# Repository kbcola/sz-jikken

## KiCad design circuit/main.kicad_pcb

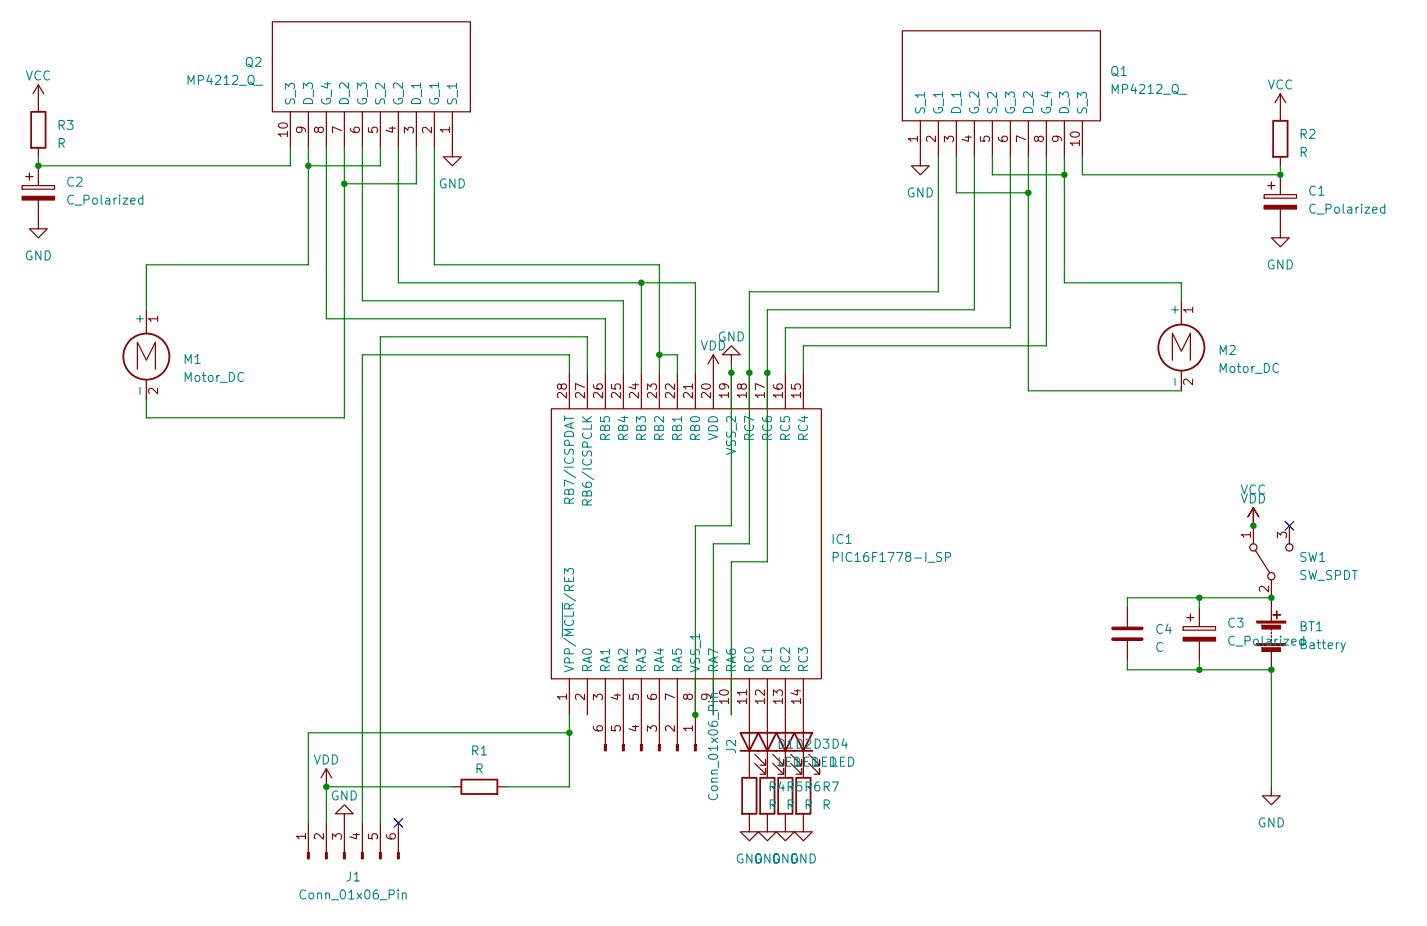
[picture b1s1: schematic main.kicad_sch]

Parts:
BT1: Battery; PinHeader_1x02_P2.54mm_Horizontal
C1, C2, C3: C_Polarized; CP_Radial_D5.0mm_P2.00mm
C4: C; C_Disc_D5.0mm_W2.5mm_P5.00mm
D1, D2, D3, D4: LED; LED_D3.0mm
IC1: PIC16F1778-I_SP; DIP-28_W7.62mm_LongPads; Manufacturer_Part_Number PIC16F1778-I/SP; Mouser Part Number 579-PIC16F1778-I/SP
J1, J2: Conn_01x06_Pin; PinHeader_1x06_P2.54mm_Vertical
M1, M2: Motor_DC; PinHeader_1x02_P2.54mm_Horizontal
Q1, Q2: MP4212_Q_; MP4212Q; Manufacturer_Part_Number MP4212(Q); Mouser Part Number N/A
R1, R4, R5, R6, R7: R; R_Axial_DIN0207_L6.3mm_D2.5mm_P7.62mm_Horizontal
R2, R3: R; R_Axial_DIN0309_L9.0mm_D3.2mm_P12.70mm_Horizontal
SW1: SW_SPDT; ToggleSW_3pin

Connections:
GND: BT1.2 (-), C1.2, C2.2, C3.2, C4.2, IC1.8 (VSS_1), IC1.19 (VSS_2), J1.3, J2.1, Q1.1 (S_1), Q2.1 (S_1), R4.2, R5.2, R6.2, R7.2
unnamed: BT1.1 (+), C3.1, C4.1, SW1.2 (B)
unnamed: D1.2 (A), IC1.11 (RC0)
unnamed: D1.1 (K), R4.1
unnamed: D2.2 (A), IC1.12 (RC1)
unnamed: D2.1 (K), R5.1
unnamed: D3.2 (A), IC1.13 (RC2)
unnamed: D3.1 (K), R6.1
unnamed: D4.2 (A), IC1.14 (RC3)
unnamed: D4.1 (K), R7.1
unnamed: IC1.3 (RA1), J2.6
unnamed: IC1.4 (RA2), J2.5
unnamed: IC1.5 (RA3), J2.4
unnamed: IC1.6 (RA4), J2.3
unnamed: IC1.7 (RA5), J2.2
unnamed: IC1.10 (RA6), IC1.17 (RC6), Q1.4 (G_2)
unnamed: IC1.9 (RA7), IC1.18 (RC7), Q1.2 (G_1)
unnamed: IC1.21 (RB0), IC1.24 (RB3), Q2.4 (G_2)
unnamed: IC1.22 (RB1), IC1.23 (RB2), Q2.2 (G_1)
unnamed: IC1.25 (RB4), Q2.6 (G_3)
unnamed: IC1.26 (RB5), Q2.8 (G_4)
unnamed: IC1.27 (RB6/ICSPCLK), J1.5
unnamed: IC1.28 (RB7/ICSPDAT), J1.4
unnamed: IC1.15 (RC4), Q1.8 (G_4)
unnamed: IC1.16 (RC5), Q1.6 (G_3)
unnamed: IC1.1 (VPP/~MCLR/RE3), J1.1, R1.2
unnamed: M1.1 (+), Q2.5 (S_2), Q2.9 (D_3)
unnamed: M1.2 (-), Q2.3 (D_1), Q2.7 (D_2)
unnamed: M2.1 (+), Q1.5 (S_2), Q1.9 (D_3)
unnamed: M2.2 (-), Q1.3 (D_1), Q1.7 (D_2)
unnamed: C1.1, Q1.10 (S_3), R2.2
unnamed: C2.1, Q2.10 (S_3), R3.2
VCC: IC1.20 (VDD), J1.2, R1.1, R2.1, R3.1, SW1.1 (A)

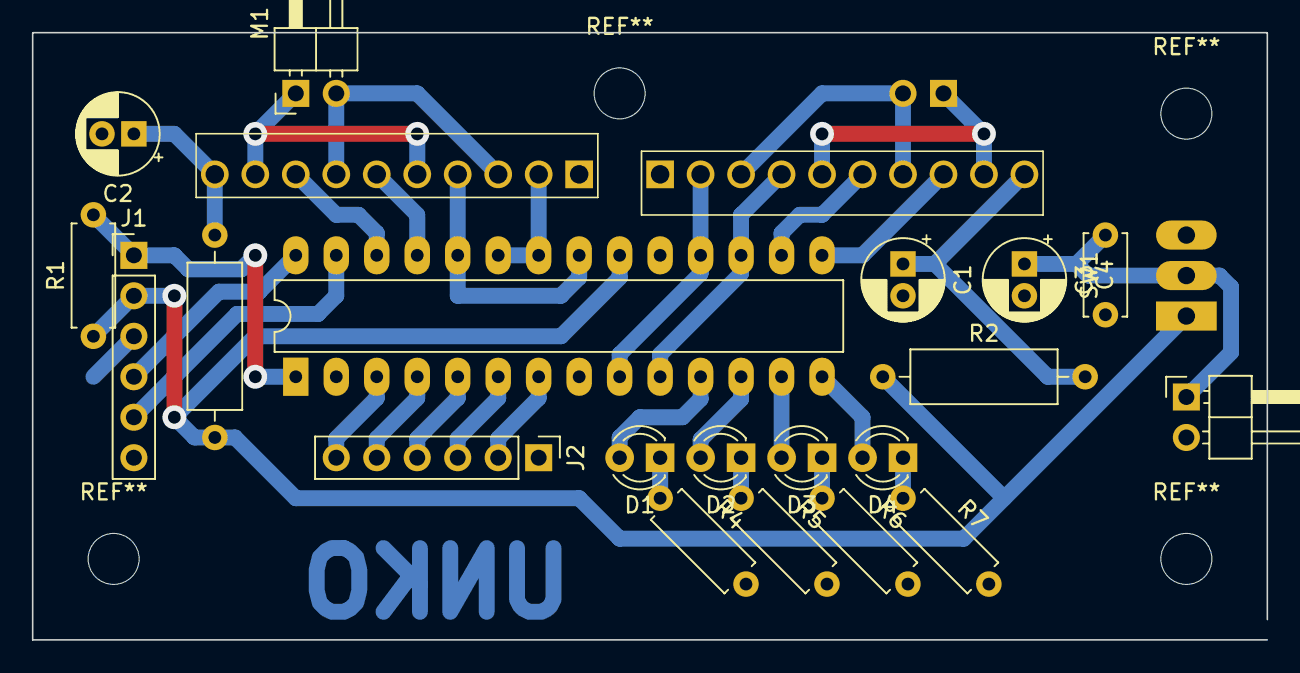
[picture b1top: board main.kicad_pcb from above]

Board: 2 copper layers, 77.5 x 38.1 mm, 24 parts (1 on the bottom side), 33 nets.

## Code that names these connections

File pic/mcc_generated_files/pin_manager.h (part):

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// get/set SAENS_LD aliases
#define SAENS_LD_TRIS                 TRISAbits.TRISA1
#define SAENS_LD_LAT                  LATAbits.LATA1
#define SAENS_LD_PORT                 PORTAbits.RA1
#define SAENS_LD_WPU                  WPUAbits.WPUA1
#define SAENS_LD_OD                   ODCONAbits.ODA1
#define SAENS_LD_ANS                  ANSELAbits.ANSA1
#define SAENS_LD_SetHigh()            do { LATAbits.LATA1 = 1; } while(0)
#define SAENS_LD_SetLow()             do { LATAbits.LATA1 = 0; } while(0)
#define SAENS_LD_Toggle()             do { LATAbits.LATA1 = ~LATAbits.LATA1; } while(0)
#define SAENS_LD_GetValue()           PORTAbits.RA1
#define SAENS_LD_SetDigitalInput()    do { TRISAbits.TRISA1 = 1; } while(0)
#define SAENS_LD_SetDigitalOutput()   do { TRISAbits.TRISA1 = 0; } while(0)
#define SAENS_LD_SetPullup()          do { WPUAbits.WPUA1 = 1; } while(0)
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// get/set SAENS_LA aliases
#define SAENS_LA_TRIS                 TRISAbits.TRISA2
#define SAENS_LA_LAT                  LATAbits.LATA2
#define SAENS_LA_PORT                 PORTAbits.RA2
#define SAENS_LA_WPU                  WPUAbits.WPUA2
#define SAENS_LA_OD                   ODCONAbits.ODA2
#define SAENS_LA_ANS                  ANSELAbits.ANSA2
#define SAENS_LA_SetHigh()            do { LATAbits.LATA2 = 1; } while(0)
#define SAENS_LA_SetLow()             do { LATAbits.LATA2 = 0; } while(0)
#define SAENS_LA_Toggle()             do { LATAbits.LATA2 = ~LATAbits.LATA2; } while(0)
#define SAENS_LA_GetValue()           PORTAbits.RA2
#define SAENS_LA_SetDigitalInput()    do { TRISAbits.TRISA2 = 1; } while(0)
#define SAENS_LA_SetDigitalOutput()   do { TRISAbits.TRISA2 = 0; } while(0)
#define SAENS_LA_SetPullup()          do { WPUAbits.WPUA2 = 1; } while(0)
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// get/set SAENS_RA aliases
#define SAENS_RA_TRIS                 TRISAbits.TRISA3
#define SAENS_RA_LAT                  LATAbits.LATA3
#define SAENS_RA_PORT                 PORTAbits.RA3
#define SAENS_RA_WPU                  WPUAbits.WPUA3
#define SAENS_RA_OD                   ODCONAbits.ODA3
#define SAENS_RA_ANS                  ANSELAbits.ANSA3
#define SAENS_RA_SetHigh()            do { LATAbits.LATA3 = 1; } while(0)
#define SAENS_RA_SetLow()             do { LATAbits.LATA3 = 0; } while(0)
#define SAENS_RA_Toggle()             do { LATAbits.LATA3 = ~LATAbits.LATA3; } while(0)
#define SAENS_RA_GetValue()           PORTAbits.RA3
#define SAENS_RA_SetDigitalInput()    do { TRISAbits.TRISA3 = 1; } while(0)
#define SAENS_RA_SetDigitalOutput()   do { TRISAbits.TRISA3 = 0; } while(0)
#define SAENS_RA_SetPullup()          do { WPUAbits.WPUA3 = 1; } while(0)
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// get/set SAENS_RD aliases
#define SAENS_RD_TRIS                 TRISAbits.TRISA4
#define SAENS_RD_LAT                  LATAbits.LATA4
#define SAENS_RD_PORT                 PORTAbits.RA4
#define SAENS_RD_WPU                  WPUAbits.WPUA4
#define SAENS_RD_OD                   ODCONAbits.ODA4
#define SAENS_RD_ANS                  ANSELAbits.ANSA4
#define SAENS_RD_SetHigh()            do { LATAbits.LATA4 = 1; } while(0)
#define SAENS_RD_SetLow()             do { LATAbits.LATA4 = 0; } while(0)
#define SAENS_RD_Toggle()             do { LATAbits.LATA4 = ~LATAbits.LATA4; } while(0)
#define SAENS_RD_GetValue()           PORTAbits.RA4
#define SAENS_RD_SetDigitalInput()    do { TRISAbits.TRISA4 = 1; } while(0)
#define SAENS_RD_SetDigitalOutput()   do { TRISAbits.TRISA4 = 0; } while(0)
#define SAENS_RD_SetPullup()          do { WPUAbits.WPUA4 = 1; } while(0)
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// get/set R0 aliases
#define R0_TRIS                 TRISAbits.TRISA6
#define R0_LAT                  LATAbits.LATA6
#define R0_PORT                 PORTAbits.RA6
#define R0_WPU                  WPUAbits.WPUA6
#define R0_OD                   ODCONAbits.ODA6
#define R0_SetHigh()            do { LATAbits.LATA6 = 1; } while(0)
#define R0_SetLow()             do { LATAbits.LATA6 = 0; } while(0)
#define R0_Toggle()             do { LATAbits.LATA6 = ~LATAbits.LATA6; } while(0)
#define R0_GetValue()           PORTAbits.RA6
#define R0_SetDigitalInput()    do { TRISAbits.TRISA6 = 1; } while(0)
#define R0_SetDigitalOutput()   do { TRISAbits.TRISA6 = 0; } while(0)
#define R0_SetPullup()          do { WPUAbits.WPUA6 = 1; } while(0)
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// get/set R1 aliases
#define R1_TRIS                 TRISAbits.TRISA7
#define R1_LAT                  LATAbits.LATA7
#define R1_PORT                 PORTAbits.RA7
#define R1_WPU                  WPUAbits.WPUA7
#define R1_OD                   ODCONAbits.ODA7
#define R1_SetHigh()            do { LATAbits.LATA7 = 1; } while(0)
#define R1_SetLow()             do { LATAbits.LATA7 = 0; } while(0)
#define R1_Toggle()             do { LATAbits.LATA7 = ~LATAbits.LATA7; } while(0)
#define R1_GetValue()           PORTAbits.RA7
#define R1_SetDigitalInput()    do { TRISAbits.TRISA7 = 1; } while(0)
#define R1_SetDigitalOutput()   do { TRISAbits.TRISA7 = 0; } while(0)
#define R1_SetPullup()          do { WPUAbits.WPUA7 = 1; } while(0)
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// get/set L0 aliases
#define L0_TRIS                 TRISBbits.TRISB0
#define L0_LAT                  LATBbits.LATB0
#define L0_PORT                 PORTBbits.RB0
#define L0_WPU                  WPUBbits.WPUB0
#define L0_ANS                  ANSELBbits.ANSB0
#define L0_SetHigh()            do { LATBbits.LATB0 = 1; } while(0)
#define L0_SetLow()             do { LATBbits.LATB0 = 0; } while(0)
#define L0_Toggle()             do { LATBbits.LATB0 = ~LATBbits.LATB0; } while(0)
#define L0_GetValue()           PORTBbits.RB0
#define L0_SetDigitalInput()    do { TRISBbits.TRISB0 = 1; } while(0)
#define L0_SetDigitalOutput()   do { TRISBbits.TRISB0 = 0; } while(0)
#define L0_SetPullup()          do { WPUBbits.WPUB0 = 1; } while(0)
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// get/set L1 aliases
#define L1_TRIS                 TRISBbits.TRISB1
#define L1_LAT                  LATBbits.LATB1
#define L1_PORT                 PORTBbits.RB1
#define L1_WPU                  WPUBbits.WPUB1
#define L1_ANS                  ANSELBbits.ANSB1
#define L1_SetHigh()            do { LATBbits.LATB1 = 1; } while(0)
#define L1_SetLow()             do { LATBbits.LATB1 = 0; } while(0)
#define L1_Toggle()             do { LATBbits.LATB1 = ~LATBbits.LATB1; } while(0)
#define L1_GetValue()           PORTBbits.RB1
#define L1_SetDigitalInput()    do { TRISBbits.TRISB1 = 1; } while(0)
#define L1_SetDigitalOutput()   do { TRISBbits.TRISB1 = 0; } while(0)
#define L1_SetPullup()          do { WPUBbits.WPUB1 = 1; } while(0)
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#define RB2_SetHigh()            do { LATBbits.LATB2 = 1; } while(0)
#define RB2_SetLow()             do { LATBbits.LATB2 = 0; } while(0)
#define RB2_Toggle()             do { LATBbits.LATB2 = ~LATBbits.LATB2; } while(0)
#define RB2_GetValue()              PORTBbits.RB2
#define RB2_SetDigitalInput()    do { TRISBbits.TRISB2 = 1; } while(0)
#define RB2_SetDigitalOutput()   do { TRISBbits.TRISB2 = 0; } while(0)
#define RB2_SetPullup()             do { WPUBbits.WPUB2 = 1; } while(0)
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#define RB3_SetHigh()            do { LATBbits.LATB3 = 1; } while(0)
#define RB3_SetLow()             do { LATBbits.LATB3 = 0; } while(0)
#define RB3_Toggle()             do { LATBbits.LATB3 = ~LATBbits.LATB3; } while(0)
#define RB3_GetValue()              PORTBbits.RB3
#define RB3_SetDigitalInput()    do { TRISBbits.TRISB3 = 1; } while(0)
#define RB3_SetDigitalOutput()   do { TRISBbits.TRISB3 = 0; } while(0)
#define RB3_SetPullup()             do { WPUBbits.WPUB3 = 1; } while(0)
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#define RB4_SetHigh()            do { LATBbits.LATB4 = 1; } while(0)
#define RB4_SetLow()             do { LATBbits.LATB4 = 0; } while(0)
#define RB4_Toggle()             do { LATBbits.LATB4 = ~LATBbits.LATB4; } while(0)
#define RB4_GetValue()              PORTBbits.RB4
#define RB4_SetDigitalInput()    do { TRISBbits.TRISB4 = 1; } while(0)
#define RB4_SetDigitalOutput()   do { TRISBbits.TRISB4 = 0; } while(0)
#define RB4_SetPullup()             do { WPUBbits.WPUB4 = 1; } while(0)
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#define RB5_SetHigh()            do { LATBbits.LATB5 = 1; } while(0)
#define RB5_SetLow()             do { LATBbits.LATB5 = 0; } while(0)
#define RB5_Toggle()             do { LATBbits.LATB5 = ~LATBbits.LATB5; } while(0)
#define RB5_GetValue()              PORTBbits.RB5
#define RB5_SetDigitalInput()    do { TRISBbits.TRISB5 = 1; } while(0)
#define RB5_SetDigitalOutput()   do { TRISBbits.TRISB5 = 0; } while(0)
#define RB5_SetPullup()             do { WPUBbits.WPUB5 = 1; } while(0)
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#define RB7_SetHigh()            do { LATBbits.LATB7 = 1; } while(0)
#define RB7_SetLow()             do { LATBbits.LATB7 = 0; } while(0)
#define RB7_Toggle()             do { LATBbits.LATB7 = ~LATBbits.LATB7; } while(0)
#define RB7_GetValue()              PORTBbits.RB7
#define RB7_SetDigitalInput()    do { TRISBbits.TRISB7 = 1; } while(0)
#define RB7_SetDigitalOutput()   do { TRISBbits.TRISB7 = 0; } while(0)
#define RB7_SetPullup()             do { WPUBbits.WPUB7 = 1; } while(0)
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// get/set LED0 aliases
#define LED0_TRIS                 TRISCbits.TRISC0
#define LED0_LAT                  LATCbits.LATC0
#define LED0_PORT                 PORTCbits.RC0
#define LED0_WPU                  WPUCbits.WPUC0
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
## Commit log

2023-07-18 kicad
2023-09-15 fix motors
2023-09-21 circuit rc1
2023-09-21 circuit rc2

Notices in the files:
pic/mcc_generated_files/pin_manager.h:
(c) 2018 Microchip Technology Inc. and its subsidiaries.
